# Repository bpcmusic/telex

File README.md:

# TELEX EURORACK EXPANDERS

The TELEX are a family of eurorack expanders that were initially designed to interface with the Monome Teletype to provide additional inputs and outputs. Utilizing the `II` bus (i2c) and having a flexible command set, there is no reason that these modules couldn't connect and extend other Monome Eurorack devices (even non-Eurorack devices that support II like the Aleph) or your own hardware projects.

Follow the conversation at [llllllll](http://llllllll.co/t/a-teletype-expander/1379).

## The Modules

The TELEXo (or TXo) is an output expander and the TELEXi (or TXi) is an input expander. They have little jumpers on the back so you can hook more than one of each module to your Teletype simultaneously. (Theoretically, up to eight of each type - though I’ve only tested six total modules at a time thus far. There will be a limit based on the II bus resistance - not sure what it is yet.)

* **TELEXo (TXo)**: a 4HP output module that provides 4 trigger outputs and 4 CV outputs addressable over `II`. Up to 8 can be independently addressed by the Teletype.

* **TELEXi (TXi)**: a 4HP input module that provides 4 control voltage potentiometers and 4 independent control voltage inputs. Up to 8 can be independently addressed by the Teletype.

## Teletype Firmware

We recommend the Teletype 2.0 BETA at this point. You can get it from this forum:

https://llllllll.co/t/teletype-2-0-beta-release-candidate-1-released-6th-june-2017/6939?u=bpcmusic

It is the bomb.

You can always head to Monome for the latest [Official Teletype Firmware](https://github.com/monome/teletype).

## TELEX Firmware

Download the latest TELEX firmware from the releases section of this site:

https://github.com/bpcmusic/telex/releases

### Installing Your Firmware

> **DO NOT POWER YOUR MODULE WHILE CONNECTING THE TEENSY VIA USB TO YOUR COMPUTER - THIS WOULD BE VERY BAD**

Ok. With that out of the way, here are some simple steps.

Firmware is loaded on the Teensy processor that piggybacks on the underside of your module. Doing so is pretty simple.

1. Download the Teensy Loader application for your operating system from https://www.pjrc.com/teensy/loader.html (if you don't have it already)
2. Download and unzip the latest TELEX firmware from https://github.com/bpcmusic/telex/releases
3. (optional) Carefully remove the Teensy from your module
4. Connect the Teensy to your computer via USB
5. Use your operating system specific instructions for the Teensy Loader to open the appropriate firmware in the Teensy loader and program it on your Teensy
6. Disconnect the Teensy from USB when the firmware has been loaded
7. Reattach the Teensy to your module if you removed it (USB port on the Teensy goes towards the top of the PCB)
8. Party.

### Compiling Your Own Firmware

Compiling the TELEX firmware is done using the [Arduino Development Environment](https://www.arduino.cc/en/Main/Software) and a few extensions.

* [Arduino Development Environment](https://www.arduino.cc/en/Main/Software)
* [Teensy-duino Add-On](https://www.pjrc.com/teensy/td_download.html)
* [i2c_t3 Library for Teensy](https://forum.pjrc.com/threads/21680-New-I2C-library-for-Teensy3)

Several additional libraries are included in the project due to the Arduino IDE's wonderful linking capabilities.

	IMPORTANT: overclock your Teensy 3.2 to 120 MHz in the IDE; Teensy 3.6 should be at 180 MHz

### Critical Startup Optimization for Compilation

> NOTE: this keeps changing in the Teensyduino application. I'm not finding this necessary anymore, but am leaving the old instructions in case anyone wants to fuss around with it. You can ignore for now.

If you want your TELEX to be ready when your Teletype has booted and is sending out the `I` script for the program that it is loading at startup, you need to make a change to the Teensy file "pins_teensy.c" in your Arduino hardware folder. For my mac, this is inside of the Arduino application package in:

`Contents\Java\hardware\teensy\avr\cores\teensy3\pins_teensy.c`

You need to change the values in the delay() calls - the original values are commented off to the right:

```
#if TEENSYDUINO >= 142
	delay(25);
	usb_init();
	delay(150); // 275
#else
	delay(50);
	usb_init();
	delay(125); // 350
#endif
```

For now, we edit this in-place. I know. We shuddered too. But, that seems to be the best way to make the change. Remember, you need to change it back for any other Arduino compilation you plan to do as it may have the device ready before all of your related components are - including the Teensy's USB interface.

## TELEX Command Reference

Reference documents for the commands supported by the TXo and TXi are located here:

* [Markdown Command Reference with Extra Descriptions](commands.md)
* [Printable Command Reference](extras/TELEX%20Command%20Reference.pdf)

The documents are a little behind the latest firmware; we're moving all operator definitions into the 2.0 documentation system which **is** up to date.

The latests ops are mentioned in this forum post, if you are curious. You need the 2.0 beta firmware (mentioned above) to access them.

https://llllllll.co/t/telex-teletype-expanders/1379/609?u=bpcmusic

## TELEXo

Each 4HP module adds 4 Trigger outputs and 4 Control Voltage outputs. 

All Teletype output functionality is supported by the TXo. Operators are near-identical for basic functionality, just put a "TO.” in front of the set you already know. The outputs are a little different; the triggers are +5V triggers and the CV outputs are bipolar (-10V to +10v) with 16 bit resolution over that range.

Extended functionality of the TXo starts with being able to specify longer values for slew and pulse times (in seconds and minutes). 

The TXo has the following “experimental” features for each of its four TR outputs:

- Configurable pulse dividers for each output
- Independent metronomes for each output that will pulse each output at intervals that can be set in milliseconds, seconds, minutes, and beats per minute (BPM)

The TXo also has the following “experimental” features for each of its four CV outputs:

- a quantizer with a dozen or so microtonal scales in addition to equal temperament
- an oscillator (not currently band-limited) that supports frequencies from LFO rates up to around 8kHz with variable morphing waveforms (sine, triangle, saw, variable width square, and noise), adjustable phase offset, and frequency slew (portamento)
- an AR (attack + release) envelope generator with times in milliseconds, seconds and minutes

These extended features, when combined together, can really push the envelope of the TXo’s processor and do some crazy stuff. For example: the output's envelope generator can act as a VCA, which turns the expander into a little 4-voice synth.

#### Links:

* [TXo Arduino Firmware](software/TELEXo)
* [TXo Module PCB](hardware/TELEXo/board)
* [TXo Module BOM](hardware/TELEXo/board/TELEXo-BOM.xlsx)
* [TXo 4HP Module Panel](hardware/TELEXo/panel)

## TELEXi

Each 4HP module adds 4 IN jacks and 4 PARAM knobs. 

* The IN jacks are bipolar (-10V to +10V).
* They jacks and knobs just like the Teletype IN and PARAM operators (TI.IN and TI.PARAM). 
* The TXi has some extended functionality where the TXi can do quantization for you and return note numbers against any one of its internal scales (there are about 12 or so). 
* Inputs are sampled with 13bit resolution.

#### Links:

* [TXo Arduino Firmware](software/TELEXi)
* [TXo Module PCB](hardware/TELEXi/board)
* [TXo Module BOM](hardware/TELEXi/board/TELEXi-BOM.xlsx)
* [TXo 4HP Module Panel](hardware/TELEXi/panel)

## Addressing Multiple TELEX Modules

Multiple TELEX modules are addressed using jumpers on the back of the unit. Theoretically, you can have up to eight of each type of unit on the same II bus. The addresses are non-conflicting between module types. For example, if you have one of each module, each would be unit #1 of that type and neither would have any address jumpers set.

The jumpers are oriented vertically and the rows are numbered from top to bottom:

* Row 1
* Row 2
* Row 3

Placing jumpers on rows in the following sequence allows you to designate the unit # (which is the binary representation of the rows plus one). X indicates the placement of a jumper.

| Row 1 | Row 2 | Row 3 | Unit # | Inputs/Outputs |
| --- | --- | --- | --- | --- |
| 0 | 0 | 0 | 1 | 1-4 |
| X | 0 | 0 | 2 | 5-8 |
| 0 | X | 0 | 3 | 9-12 |
| X | X | 0 | 4 | 13-16 |
| 0 | 0 | X | 5 | 17-20 |
| X | 0 | X | 6 | 21-24 |
| 0 | X | X | 7 | 25-28 |
| X | X | X | 8 | 28-32 |

## DIY Tips and Warnings

The modules are made up with two boards stacked on top of each other and a Teensy 3.2 riding piggyback. They are primarily 603 SMD parts with a few 805, 1206 and SMD ICs thrown in for good measure. If you have assembled any of mxmxmx’s DIY modules (Ornament + Crime, Terminal Tedium, etc.) you should have no problem with the expanders. They are not, however, a beginners project for SMD.

The DAC that is used for the TXo is the DAC8564 (Mouser P/N: 595-DAC8564ICPW; datasheet: http://www.ti.com/product/DAC8564). This part is used by a number of Eurorack modules - including Mutable's *Yarns* and *Ornament + Crime* by mxmxmx. It has tiny little SMD legs that can cause DIY cursing. ;)

#### Use the Build Maps

The build maps are PDF files that have one page per component per side per board showing you all the places that component goes. This saves a ton of time and avoids the pain-in-the-ass component hunt. They are linked below - but check out the example below:

Thanks to [c1t1zen](https://www.instagram.com/c1t1zen/) for the idea. :)

#### Crazy Board Naming

I have a goofy naming convention for the boards. It is confusing. But, I embraced the organic silliness. The "Top" Board is the one behind the panel. The "Bottom" Board is the one facing the back of your case. The side of the board with the name of the unit and board on it is considered the "Top" of the board. The other side is considered the bottom. This means The boards and sides are like this:

- **Top Top** - facing the panel; has the jacks, pots and LEDs
- **Top Bottom** - the back-side of the one facing the panel with a small handful of components
- **Bottom Bottom** - faces the Top Bottom on the "back board" of the unit
- **Bottom Top** - faces the back of your case; has the Teensy, power and jumpers mounted on it

Stupid, I know. But it makes a certain kind of back assward sense.

#### Balancing Headers IMPORTANT

In addition to the two signal headers that connect the boards, there are a pair of two pin connectors that provide balance at the top and the bottom of the boards. Keep the following tips in mind:

> The top connector for both modules needs to be installed before the component that it sits behind it is placed. The header pins on the Top Top side should be as near flush as possible. They aid in connecting both boards ground planes, so you don't want them shorting out to the jack (TXo) or the potentiometer (TXi). I actually trim them to be board-level prior to soldering so that they are as flat as possible. I also bend the front foot of the potentiometer (TXi) out of the way a bit so as to avoid contact.

#### Stencil Frames are your Friends

There are a bunch of 3D printable frames available for you to help your build process. As there are SMD components on both sides of the three of the four boards across the two modules, these frames help lay the boards flat for the application of solder paste and/or manual soldering of the components. They save you a ton of time and frustration. They are your friends.

There are also MULTI files for three of the dual-sided boards that will help you hold eight boards next to each other at a time. These are really handy if you are building in bulk. All of the files are in the stencil_frame folders inside of the hardware / board folders.

3D Prints were tested on a Prusa i3 MK2 with PLA filament.

### TXi Build Files

[Explore the repository for all kinds of support files](hardware/TELEXi). Here are some of the key ones:

* [TXi Schematic](hardware/TELEXi/board/Telex-I%20Schematic.pdf)
* [TXi Gerbers Top](hardware/TELEXi/board/gerbers/TI-TOP-1.1.zip)
* [TXi Gerbers Bottom](hardware/TELEXi/board/gerbers/TI-BOT%201.1A.zip)
* [TXi BOM](hardware/TELEXi/board/TELEXi-BOM.xlsx)
* [TXi Bottom Top Build Map](hardware/TELEXi/board/build_map/bt/txi_bt_build_map.pdf)
* [TXi Bottom Bottom Build Map](hardware/TELEXi/board/build_map/bb/txi_bb_build_map.pdf)
* [TXi Top Top Build Map](hardware/TELEXi/board/build_map/tt/txi_tt_build_map.pdf)
* [TXi Top Bottom Build Map](hardware/TELEXi/board/build_map/tb/txi_tb_build_map.pdf)
* [TXi Panel Files](hardware/TELEXi/panel)
* [TXi Stencil Frames](hardware/TELEXi/board/stencil_frame)

### TXo Build Files

[Explore the repository for all kinds of support files](hardware/TELEXo). Here are some of the key ones:

* [TXo Schematic](hardware/TELEXo/board/Telex-O%20Schematic.pdf)
* [TXo Gerbers Top](hardware/TELEXo/board/gerbers/TO-TOP-1.1.zip)
* [TXo Gerbers Bottom](hardware/TELEXo/board/gerbers/TO-BOT-1.1.zip)
* [TXo BOM](hardware/TELEXo/board/TELEXo-BOM.xlsx)
* [TXo Bottom Top Build Map](hardware/TELEXo/board/build_map/bt/txo_bt_build_map.pdf)
* [TXo Bottom Bottom Build Map](hardware/TELEXo/board/build_map/bb/txo_bb_build_map.pdf)
* [TXo Top Top Build Map](hardware/TELEXo/board/build_map/tt/txo_tt_build_map.pdf)
* [TXo Top Bottom Build Map](hardware/TELEXo/board/build_map/tb/txo_tb_build_map.pdf)
* [TXo Panel Files](hardware/TELEXo/panel)
* [TXo Stencil Frames](hardware/TELEXo/board/stencil_frame)

## Thanks
* Brian Crabtree and Kelli Cain for creating [Monome](http://monome.org) and their awesome, open Eurorack modules (including the Teletype which started this all).

* [Galapagoose](http://llllllll.co/users/galapagoose/activity) for being an endlessly patient mentor helping get the circuit design and layout sorted. These modules wouldn't exist without his help.

* [Tom Erbe](http://www.soundhack.com/) for teaching me all about this stuff at CalArts back in the dark ages.

* Ezra Buchla and Brian for birthing the beautiful and ambitious Aleph and endowing it with an `II` jack.

* Tom Whitwell of [Music Thing Modular](http://musicthing.co.uk/modular/) and his open sharing of the Teensy 3.1 powered, Bad-Assed [RadioMusic](https://github.com/TomWhitwell/RadioMusic/wiki).

* Émilie Gillet at [Mutable Instruments](http://mutable-instruments.net/) for her fantastic modules, excellent design, impressive implementation skills and commitment to open hardware. 

* Jim Matheson of Neutron Sound and his fantastic Teensy 3.1 powered [Orgone Accumulator](http://neutron-sound.com/noa.html).

* PJRC for making the awesome [Teensy](https://www.pjrc.com/teensy/index.html).

* The community at [llllllll](http://llllllll.co) for being so supportive and patient as I've lumbered my way through making these things.

---

These modules are open source. Hardware is released under the cc-by-sa-4.0 license and the source code is released under the MIT license.

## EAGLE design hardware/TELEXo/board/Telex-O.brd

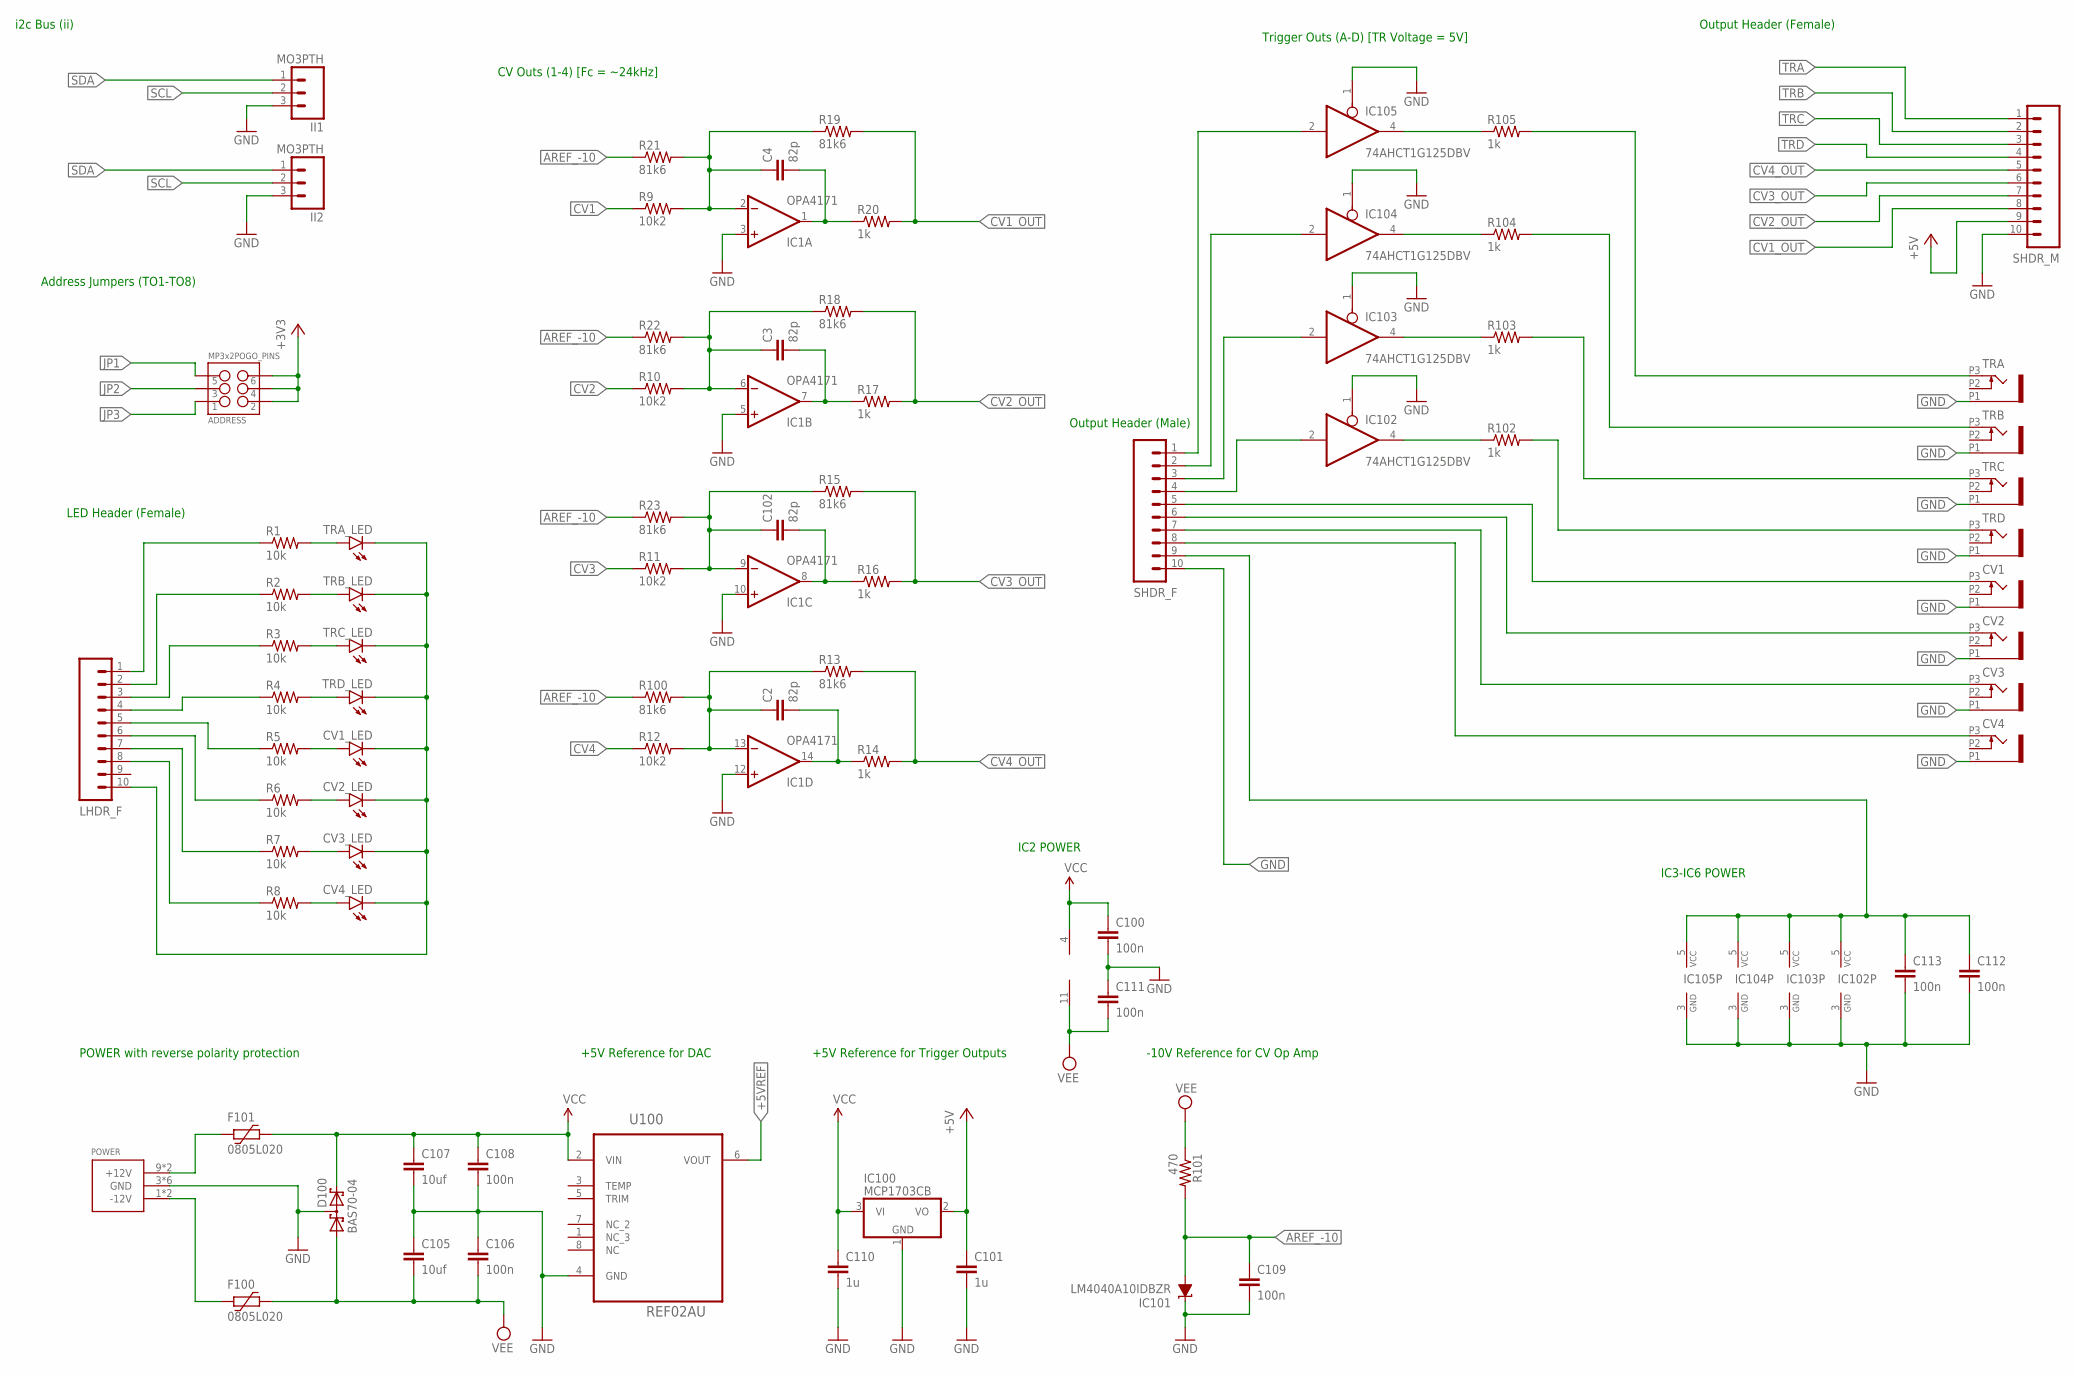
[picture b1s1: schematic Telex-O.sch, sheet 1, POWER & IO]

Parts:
ADDRESS: MP3x2POGO_PINS; 2X3_POGO
C2, C3, C4, C102: 82p; 1206
C100, C106, C108, C109, C111, C112, C113: 100n; 0603-CAP
C101, C110: 1u; 0603-CAP
C105, C107: 10uf; 1206
CV1, CV2, CV3, CV4: EURO_JACKS-7; WQP_PJ_301M
CV1_LED, CV2_LED, CV3_LED, CV4_LED: LED3MM
D100: BAS70-04; SOT23
F100, F101: 0805L020; 0805L
IC1: OPA4171; SO14
IC100: MCP1703CB; SOT23
IC101: LM4040A10IDBZR; DBZ_R-PDSO-G3
IC102, IC103, IC104, IC105: 74AHCT1G125DBV; SOT23-5
II1, II2: MO3PTH; 1X03
LHDR_F: M10SILK_FEMALE_PTH; 1X10
POWER: 10-Pin; POWER_10
R1, R2, R3, R4, R5, R6, R7, R8: 10k; R0603
R9, R10, R11, R12: 10k2; R0603
R13, R15, R18, R19, R21, R22, R23, R100: 81k6; R0603
R14, R16, R17, R20, R102, R103, R104, R105: 1k; R0603
R101: 470; R0603
SHDR_F: M10SILK_FEMALE_PTH; 1X10
SHDR_M: M10SILK_FEMALE_PTH; 1X10
TRA: EURO_JACKS-7; WQP_PJ_301M
TRA_LED: LED3MM
TRB: EURO_JACKS-7; WQP_PJ_301M
TRB_LED: LED3MM
TRC: EURO_JACKS-7; WQP_PJ_301M
TRC_LED: LED3MM
TRD: EURO_JACKS-7; WQP_PJ_301M
TRD_LED: LED3MM
U100: REF02AU; SOIC127P600X175-8N

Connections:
+3V3: ADDRESS.P$2 (2), ADDRESS.P$4 (4), ADDRESS.P$6 (6); also elsewhere on the board
+5V: C101.1, IC100.2 (VO), SHDR_M.9; also elsewhere on the board
+5VREF: U100.6 (VOUT); also elsewhere on the board
AREF_-10: C109.1, IC101.2 (A), R21.1, R22.1, R23.1, R100.1, R101.2
CV1: R9.1; also elsewhere on the board
CV1_OUT: R19.2, R20.2, SHDR_M.8
CV2: R10.1; also elsewhere on the board
CV2_OUT: R17.2, R18.2, SHDR_M.7
CV3: R11.1; also elsewhere on the board
CV3_OUT: R15.2, R16.2, SHDR_M.6
CV4: R12.1; also elsewhere on the board
CV4_OUT: R13.2, R14.2, SHDR_M.5
GND: C100.2, C101.2, C105.1, C106.1, C107.2, C108.2, C109.2, C110.2, C111.1, C112.2, C113.2, CV1.P1 (1), CV1_LED.K (C), CV2.P1 (1), CV2_LED.K (C), CV3.P1 (1), CV3_LED.K (C), CV4.P1 (1), CV4_LED.K (C), D100.3 (C1A2), IC1.3 (+IN), IC1.5 (+IN), IC1.10 (+IN), IC1.12 (+IN), IC100.1 (GND), IC101.1 (C), IC102.1 (OE), IC102.3 (GND), IC103.1 (OE), IC103.3 (GND), IC104.1 (OE), IC104.3 (GND), IC105.1 (OE), IC105.3 (GND), II1.3, II2.3, LHDR_F.10, POWER.3 (GND), POWER.4 (GND), POWER.5 (GND), POWER.6 (GND), POWER.7 (GND), POWER.8 (GND), SHDR_F.10, SHDR_M.10, TRA.P1 (1), TRA_LED.K (C), TRB.P1 (1), TRB_LED.K (C), TRC.P1 (1), TRC_LED.K (C), TRD.P1 (1), TRD_LED.K (C), U100.4 (GND); also elsewhere on the board
JP1: ADDRESS.P$5 (5); also elsewhere on the board
JP2: ADDRESS.P$3 (3); also elsewhere on the board
JP3: ADDRESS.P$1 (1); also elsewhere on the board
M$22: C4.1, IC1.2 (-IN), R9.2, R19.1, R21.2
unnamed: F101.2, POWER.9 (+12V), POWER.10 (+12V)
unnamed: F100.2, POWER.1 (-12V), POWER.2 (-12V)
unnamed: CV4_LED.A, R8.2
unnamed: IC105.2 (I), SHDR_F.1
unnamed: CV3_LED.A, R7.2
unnamed: CV2_LED.A, R6.2
unnamed: CV1_LED.A, R5.2
unnamed: R4.2, TRD_LED.A
unnamed: R3.2, TRC_LED.A
unnamed: R2.2, TRB_LED.A
unnamed: R1.2, TRA_LED.A
unnamed: IC104.2 (I), SHDR_F.2
unnamed: IC103.2 (I), SHDR_F.3
unnamed: C4.2, IC1.1 (OUT), R20.1
unnamed: IC102.2 (I), SHDR_F.4
unnamed: C3.2, IC1.7 (OUT), R17.1
unnamed: C3.1, IC1.6 (-IN), R10.2, R18.1, R22.2
unnamed: R102.2, TRD.P3 (3)
unnamed: R103.2, TRC.P3 (3)
unnamed: C102.2, IC1.8 (OUT), R16.1
unnamed: C102.1, IC1.9 (-IN), R11.2, R15.1, R23.2
unnamed: LHDR_F.1, R1.1
unnamed: C2.2, IC1.14 (OUT), R14.1
unnamed: C2.1, IC1.13 (-IN), R12.2, R13.1, R100.2
unnamed: LHDR_F.2, R2.1
unnamed: LHDR_F.3, R3.1
unnamed: LHDR_F.4, R4.1
unnamed: IC102.4 (O), R102.1
unnamed: IC103.4 (O), R103.1
unnamed: IC104.4 (O), R104.1
unnamed: IC105.4 (O), R105.1
unnamed: R104.2, TRB.P3 (3)
unnamed: R105.2, TRA.P3 (3)
unnamed: C112.1, C113.1, IC102.5 (VCC), IC103.5 (VCC), IC104.5 (VCC), IC105.5 (VCC), SHDR_F.9
unnamed: CV3.P3 (3), SHDR_F.7
unnamed: LHDR_F.5, R5.1
unnamed: LHDR_F.6, R6.1
unnamed: LHDR_F.7, R7.1
unnamed: LHDR_F.8, R8.1
unnamed: CV1.P3 (3), SHDR_F.5
unnamed: CV2.P3 (3), SHDR_F.6
unnamed: CV4.P3 (3), SHDR_F.8
SCL: II1.2, II2.2; also elsewhere on the board
SDA: II1.1, II2.1; also elsewhere on the board
TRA: SHDR_M.1; also elsewhere on the board
TRB: SHDR_M.2; also elsewhere on the board
TRC: SHDR_M.3; also elsewhere on the board
TRD: SHDR_M.4; also elsewhere on the board
VCC: C100.1, C107.1, C108.1, C110.1, D100.2 (C2), F101.1, IC1.4 (V+), IC100.3 (VI), U100.2 (VIN)
VEE: C105.2, C106.2, C111.2, D100.1 (A1), F100.1, IC1.11 (V-), R101.1

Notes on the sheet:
POWER with reverse polarity protection
i2c Bus (ii)
LED Header (Female)
Address Jumpers (TO1-TO8)
CV Outs (1-4) [Fc = ~24kHz]
Trigger Outs (A-D) [TR Voltage = 5V]
IC2 POWER
IC3-IC6 POWER
Output Header (Male)
Output Header (Female)
+5V Reference for DAC
+5V Reference for Trigger Outputs
-10V Reference for CV Op Amp

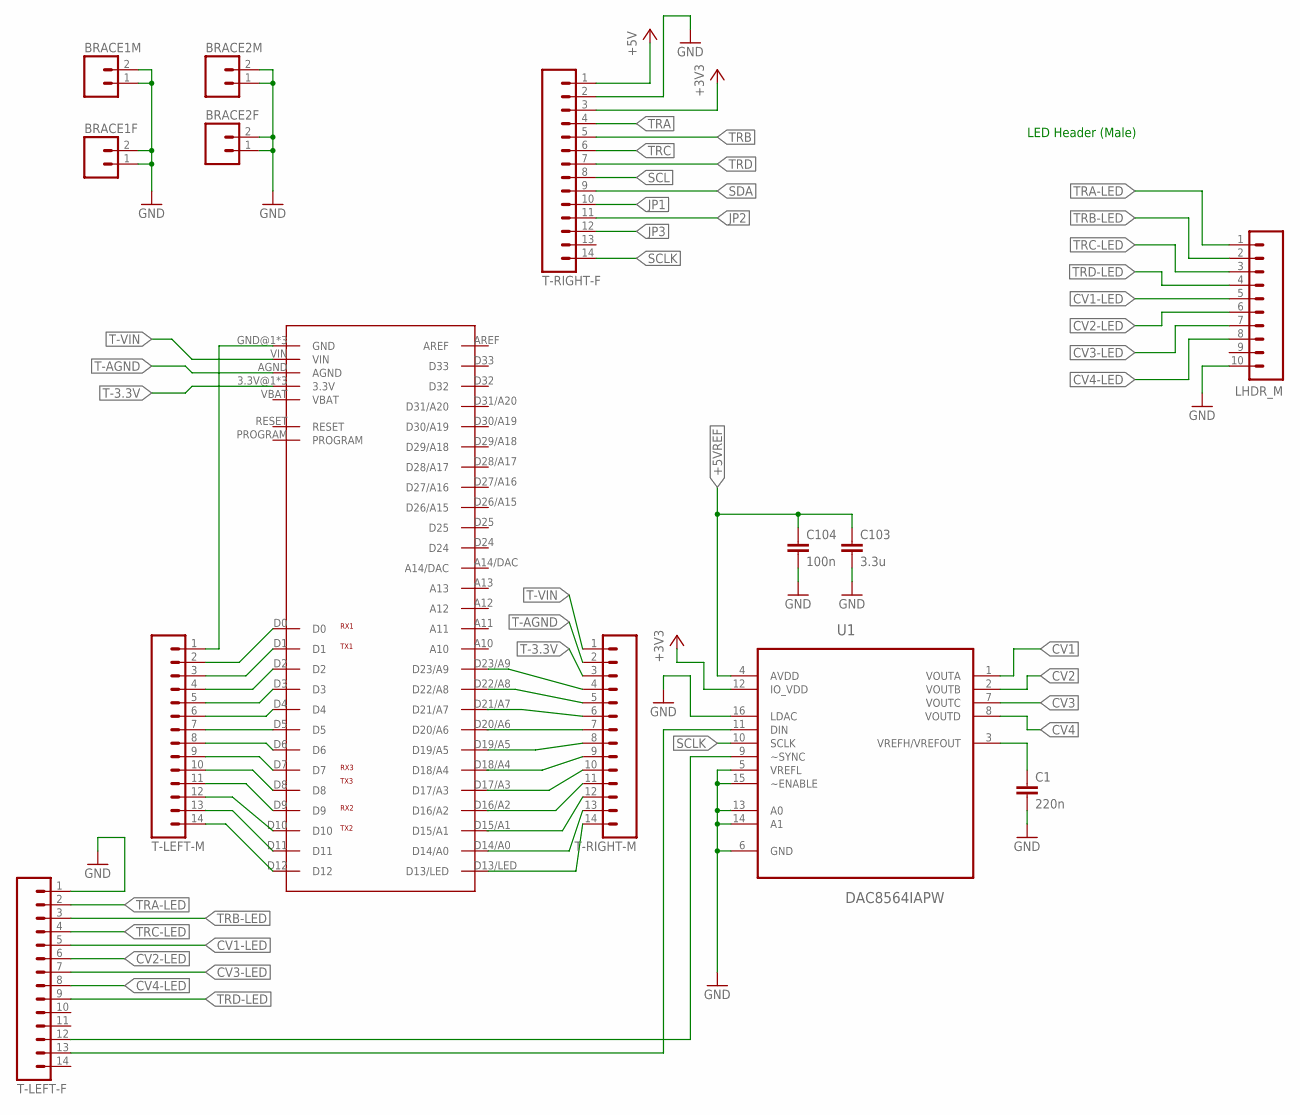
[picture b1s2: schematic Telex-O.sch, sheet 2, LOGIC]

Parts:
BRACE1F, BRACE1M, BRACE2F, BRACE2M: M02PTH; 1X02
C1: 220n; 0603-CAP
C103: 3.3u; 1206
C104: 100n; 0603-CAP
LHDR_M: M10SILK_FEMALE_PTH; 1X10
T-LEFT-F: M14; 1X14
T-LEFT-M: M14; 1X14
T-RIGHT-F: M14; 1X14
T-RIGHT-M: M14; 1X14
U1: DAC8564IAPW; SOP65P640X120-16N
U$1: TEENSY3.1_ALL

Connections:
+3V3: T-RIGHT-F.3, U1.12 (IO_VDD); also elsewhere on the board
+5V: T-RIGHT-F.1; also elsewhere on the board
+5VREF: C103.1, C104.1, U1.4 (AVDD); also elsewhere on the board
CV1: U1.1 (VOUTA); also elsewhere on the board
CV1-LED: LHDR_M.5, T-LEFT-F.5
CV2: U1.2 (VOUTB); also elsewhere on the board
CV2-LED: LHDR_M.6, T-LEFT-F.6
CV3: U1.7 (VOUTC); also elsewhere on the board
CV3-LED: LHDR_M.7, T-LEFT-F.7
CV4: U1.8 (VOUTD); also elsewhere on the board
CV4-LED: LHDR_M.8, T-LEFT-F.8
GND: BRACE1F.1, BRACE1F.2, BRACE1M.1, BRACE1M.2, BRACE2F.1, BRACE2F.2, BRACE2M.1, BRACE2M.2, C1.2, C103.2, C104.2, LHDR_M.10, T-LEFT-F.1, T-RIGHT-F.2, U1.5 (VREFL), U1.6 (GND), U1.13 (A0), U1.14 (A1), U1.15 (~ENABLE), U1.16 (LDAC); also elsewhere on the board
JP1: T-RIGHT-F.10; also elsewhere on the board
JP2: T-RIGHT-F.11; also elsewhere on the board
JP3: T-RIGHT-F.12; also elsewhere on the board
unnamed: T-RIGHT-M.14, U$1.D13/LED
unnamed: T-LEFT-F.12, U1.9 (~SYNC)
unnamed: T-LEFT-F.13, U1.11 (DIN)
unnamed: C1.1, U1.3 (VREFH/VREFOUT)
unnamed: T-LEFT-M.2, U$1.D0
unnamed: T-LEFT-M.3, U$1.D1
unnamed: T-LEFT-M.4, U$1.D2
unnamed: T-LEFT-M.5, U$1.D3
unnamed: T-LEFT-M.6, U$1.D4
unnamed: T-LEFT-M.7, U$1.D5
unnamed: T-LEFT-M.8, U$1.D6
unnamed: T-LEFT-M.9, U$1.D7
unnamed: T-LEFT-M.12, U$1.D10
unnamed: T-LEFT-M.13, U$1.D11
unnamed: T-LEFT-M.1, U$1.GND@1 (GND), U$1.GND@2 (GND), U$1.GND@3 (GND)
unnamed: T-LEFT-M.10, U$1.D8
unnamed: T-LEFT-M.11, U$1.D9
unnamed: T-LEFT-M.14, U$1.D12
unnamed: T-RIGHT-M.13, U$1.D14/A0
unnamed: T-RIGHT-M.8, U$1.D19/A5
unnamed: T-RIGHT-M.5, U$1.D22/A8
unnamed: T-RIGHT-M.4, U$1.D23/A9
SCL: T-RIGHT-F.8; also elsewhere on the board
SCLK: T-RIGHT-F.14, U1.10 (SCLK)
SDA: T-RIGHT-F.9; also elsewhere on the board
T-3.3V: T-RIGHT-M.3, U$1.3.3V@1 (3.3V), U$1.3.3V@2 (3.3V), U$1.3.3V@3 (3.3V)
T-AGND: T-RIGHT-M.2, U$1.AGND
T-VIN: T-RIGHT-M.1, U$1.VIN
TRA: T-RIGHT-F.4; also elsewhere on the board
TRA-LED: LHDR_M.1, T-LEFT-F.2
TRB: T-RIGHT-F.5; also elsewhere on the board
TRB-LED: LHDR_M.2, T-LEFT-F.3
TRC: T-RIGHT-F.6; also elsewhere on the board
TRC-LED: LHDR_M.3, T-LEFT-F.4
TRD: T-RIGHT-F.7; also elsewhere on the board
TRD-LED: LHDR_M.4, T-LEFT-F.9

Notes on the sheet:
LED Header (Male)

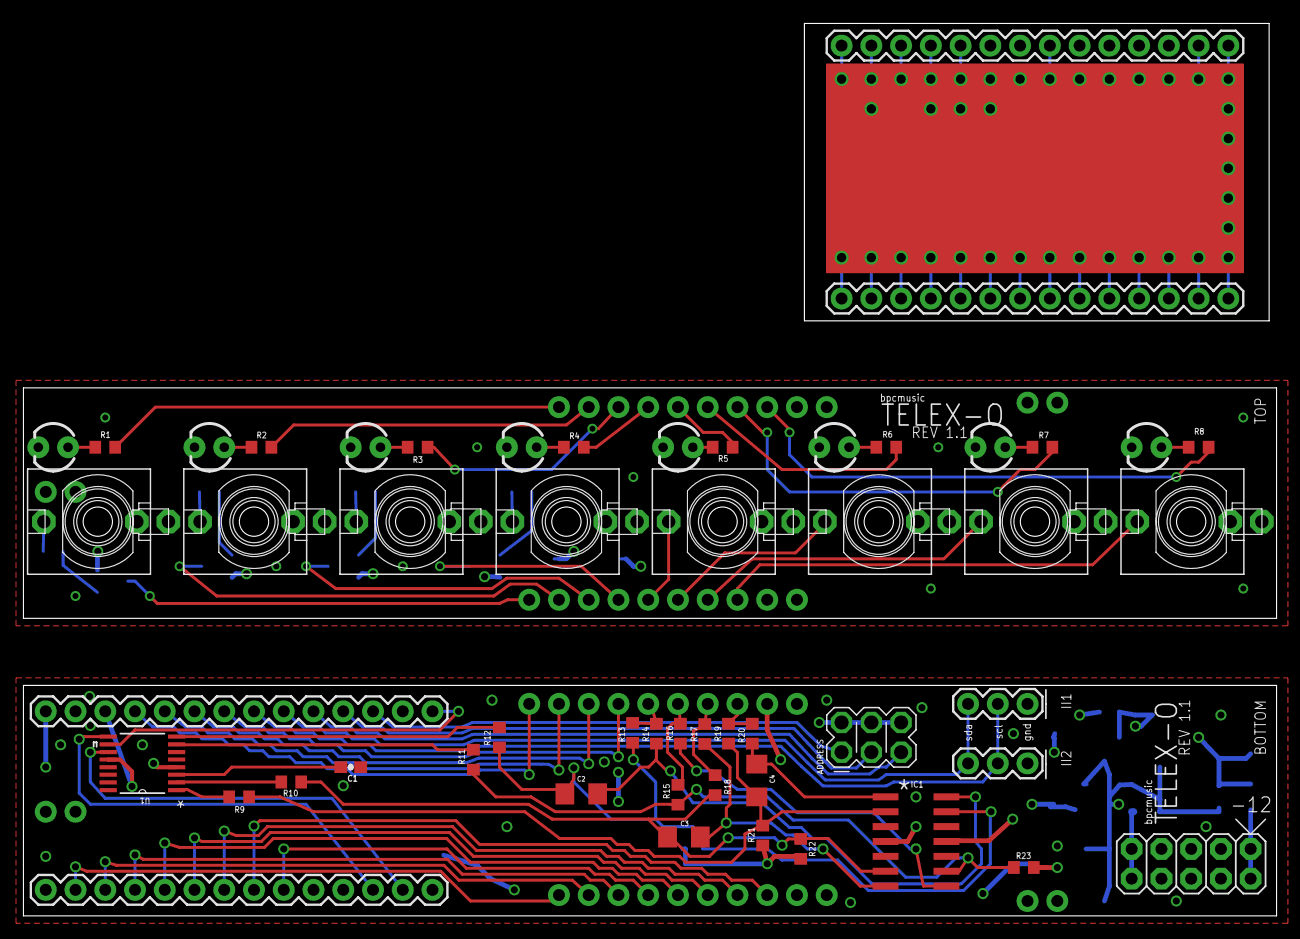
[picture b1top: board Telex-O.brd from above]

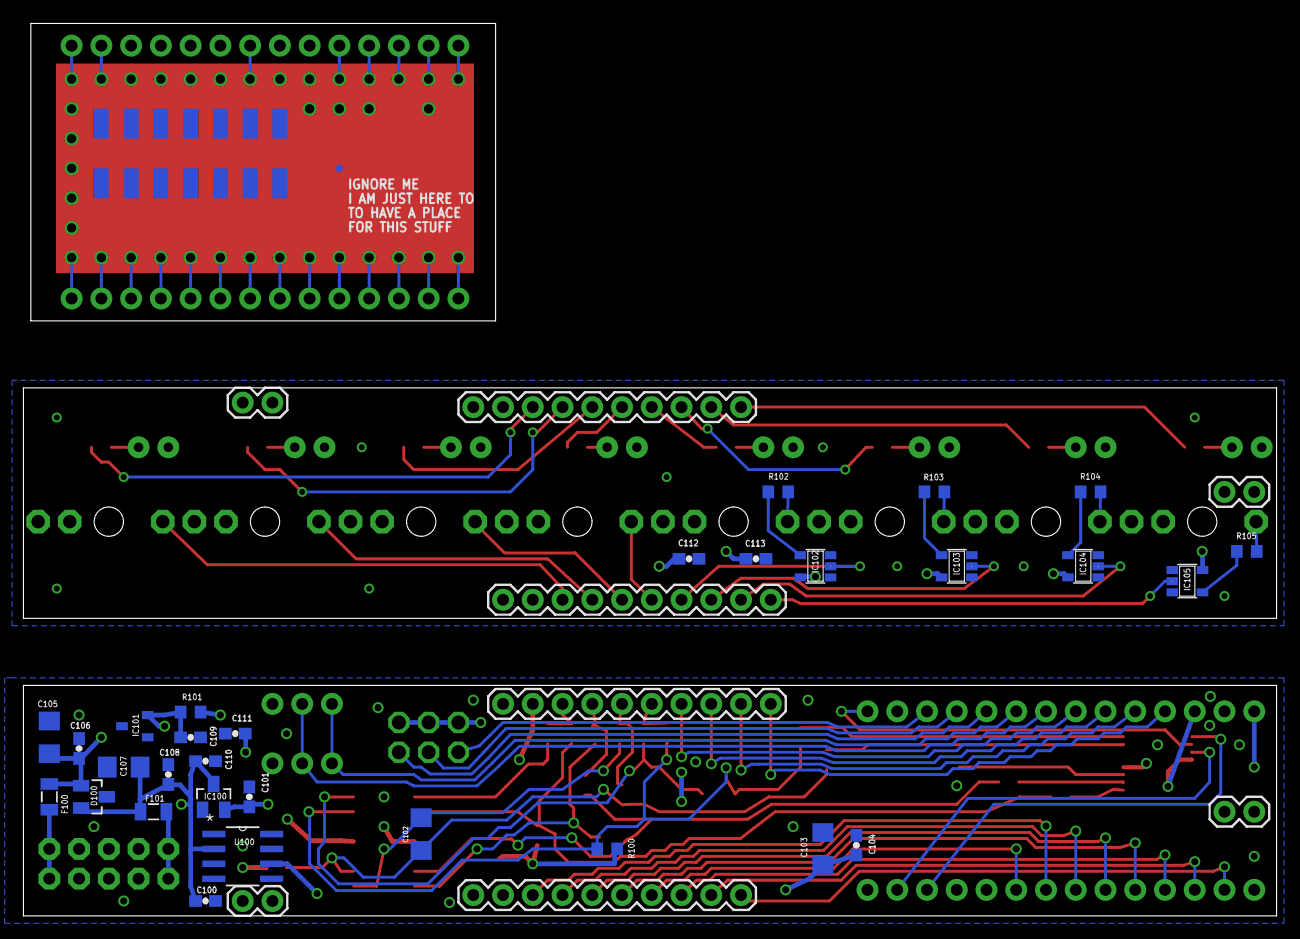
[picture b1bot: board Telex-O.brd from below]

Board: 4 copper layers, 107.0 x 76.2 mm, 92 parts (38 on the bottom side), 101 nets.

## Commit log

2016-12-27 added (c) notice
2016-12-28 updated panel art
2016-12-29 added PDF of schematic
2016-12-30 updated AI file and added mock-up PNG files
2017-01-02 added info for addressing multiple modules
2017-01-08 added a bunch of supporting materials (some in-progress) and updated the command documentation
2017-01-13 set i2c to 400mHz; TXi build maps; assembly_frame thing
2017-01-14 build maps and updated BOMs
2017-01-14 changed i2c pullup value from test
2017-01-14 fixed a couple of links
2017-01-15 added some margin to the stencil frame, updated the TELEX header file and made a global for pullup
2017-01-15 added code for metronomes and pulse dividers
2017-02-02 bugfixes for envelopes and some 3d printed build stuff added
2017-02-03 wave morphing
2017-02-06 osc phase offset
2017-02-07 working changes
2017-02-07 phasing merge fix
2017-02-07 fixed LED issue for specific sequence of positive and negative values; optimized oscillator phase code
2017-02-07 telex BOM update; command-reference update
2017-02-09 updated the readme and commented the debug flag in the TXi software
2017-02-12 updated build map for typo and added the multi-board frames with proper spacing
2017-02-12 updated readme with more build tips
2017-02-13 expanded tolerances for jacks and LEDs
2017-02-18 added functions for TI mapping, CYC setting of oscillation and trigger width percentage of TR.M
2017-02-18 β instead
2017-02-18 added count parameter and an LED brightness slope
2017-02-23 updated readme with teletype firmware details
2017-03-21 updated assembly frame, BOMs and TriggerOutput behavior for TR.M
2017-05-02 Fix command reference link.
2017-05-05 Markdown fixes.
2017-05-07 documentation details
2017-05-08 MD header format fix.
2017-05-08 more readme formatting fixes
2017-05-11 Update commands.md
    Fixing formatting.
2017-05-27 updates for v.14 of the TELEXo code
2017-06-03 New Telex Operators:
    - TO.TR.PULSE.MUTE/TO.TR.P.MUTE - mute/unmute a TR PULSE output
    - TO.TR.INIT/TO.CV.INIT/TO.INIT - all are now device native
    - TO.OSC.CTR - set the centerpoint for oscillation
    - TO.ENV.EOR/TO.ENV.EOC - bind local trigger outputs to points in the envelope
    - TO.M.ACT - global activation for all 4 metronomes
    - TO.M - set the ms rate for all 4 metronomes
2017-06-03 micro bug with offsets when envelope is being triggered
2017-06-09 optimized memory and fixed mid-envelope rate updates
2017-06-11 added details for the start-up speed optimization
2017-06-11 notes for installing firmware
2017-07-07 mid-process update for TXi
2017-07-17 Add orientation of Teensy to firmware update instructions in readme
2017-11-16 updated build map and BOM for 1k trigger out resistor reversion; massively improved the smoothing method for the TXi reads; added back the Teensy-specific i2c library for the TXo (oops)
2017-11-20 documentation update for 2nd run
2017-12-03 updated txi code to fix bug in calibration and reduce sampling interval to 1ms
2018-01-09 v.019 BETA - bug fixes for CV, jumper settings, and new envelope operators
2018-01-22 fixes for TXi address identification
2018-02-22 updated BOM files
2018-02-24 envelope fix, refactoring, inital 3.6 support, new wavetables
2018-03-02 bom fix; txo envelope recomputation enhancement; telexi smoothing enhancement
2018-03-18 initial polyblep test
2018-03-19 interim PolyBlep optimizations for fixed point - lots of test code in here
2018-03-19 fixed point polyblep implementation for saw and square
2018-03-19 implemented fixed point polyblep for saw and square waves on txo+
2018-03-19 switched to native generation of sawtooth wave
2018-03-19 optimizations for triangle wave
2018-03-19 added yummy oscillator stuff to the morphing destination waveform
2018-03-21 optomized primary and morph wave playback
2018-03-23 further slight speed and quality enhancements for triangle, saw, and square wave creation
2018-04-20 Fix command ref link.
2018-09-01 slight changes to the readme
2021-09-18 fixed pulse width function

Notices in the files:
parts and their libraries:
SparkFun-Connectors: Licensing: Creative Commons ShareAlike 4.0 International - https://creativecommons.org/licenses/by-sa/4.0
